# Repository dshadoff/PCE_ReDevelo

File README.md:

# PCE_ReDevelo
A new set of hardware and support code based on Tokumashoten Intermedia's "Develo" magazines from 1996

In 1996, Tokumashoten Intermedia released several "MOOKs" (Magazine-style Books) related
to "Develo System". One for Assembler, one for BASIC, and two issues of a magazine which
followed.  The concept was that everyday users could learn how to program (or develop art
and/or music) for the PC Engine, and somehow they could eventually develop games of their own.

The "Develo System" consisted of three pieces:
1. Software on the PC Engine side (a CD-ROM included with the MOOK)
2. Software on the PC side (targetted at MSX and PC-98 series computers)
3. A small piece of hardware which was used to connect the two systems.  On the PC Engine
   side, it conected to the joypad port (while allowing pass-through for regular
   joypad use), and on the computer side, it connected to the printer port and RS-232
   port of the PC-98 (printer port and "Port2" of MSX).

Back in the day, I wasn't able to get this to work because the IBM PC systems available
in the West were not quite compatible with the PC-98. Also, I didn't know any Japanese,
and all of the documentation was in Japanese.

A version for IBM PC eventually came out, but the release packages were in an obscure
delta patch format sepcific to Japan, and the documentation was still all in Japanese.
I wasn't able to get it working to my satisfaction.

In 1998 or so, David Michel (author of the famous MagicEngine PC Engine emulator) released
an assembler package, which included some basic support for Develo, and I was able to
download the data on the disc, but I didn't do much more than that.

Years later, and computer nowadays don't normally have the same ports, and won't run the
same 16-bit progrmas from back then, so nothing from that time will work - unless you
manage to obtain old machines and put them to use.

This was the inspiration for the ReDevelo system I have created, which also consists of three pieces:
1. Software on the PC Engine side (use the original from the MOOK)
2. Software on the PC side (in Python, for flexibility)
3. A small piece of hardware to connect the two systems (and corresponding firmware).
   Plans are provided, including enough information for small-run production of the PC Boards.

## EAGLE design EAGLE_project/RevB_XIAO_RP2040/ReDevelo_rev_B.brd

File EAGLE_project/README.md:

# PCE_ReDevelo - PC Boards

Here, you will find EAGLE project files for version of the board I have made/used.

The EAGLE project files are included, plus the gerbers and even the PCB assembly files
which might be useful for submission to JLCPCB (these are the BOM and assembly csv files).

### Revision A - Adafruit M0 Adalogger

This was the initial board I used, as I was familiar with it, and have made several designs
based on the board.  However, it has some features which I didn't end up using (and a cost
to go along with those features).

I ended up switching to the Seeeduino XIAO because this is basically a straightforward project.
So far, all code will work on both boards, but my target platform from now on will be the 'Rev B'
hardware, so this board may stop being supported at some point.

### Revision B - Seeeduino XIAO M0

As this project is straightforward, I decided to aim for a board with broad availability and
a low price (as well as a small footprint), so I chose the Seeeduino XIAO M0, which retails
for around US$5.50 .  This device is supported by the Arduino ecosystem, which is used by this
project at the current time.

In future, I may switch over to the Seeeduino XIAO RP2040 - which could sit on the same board,
but if I do that, I would port the Arduino code to the pico-sdk.

In this board revision, I have made the pads larger so that you can choose whether to mount the
XIAO M0 in a socket, or flush with the board (as the XIAO is castellated, and can be soldered
directly to the carrier board).  I also placed mounting holes in preparation for a 3D-printed
case, but have not yet designed one.  (One a case is designed, there may need to be another
board revision to accommodate the physical requirements of the case).

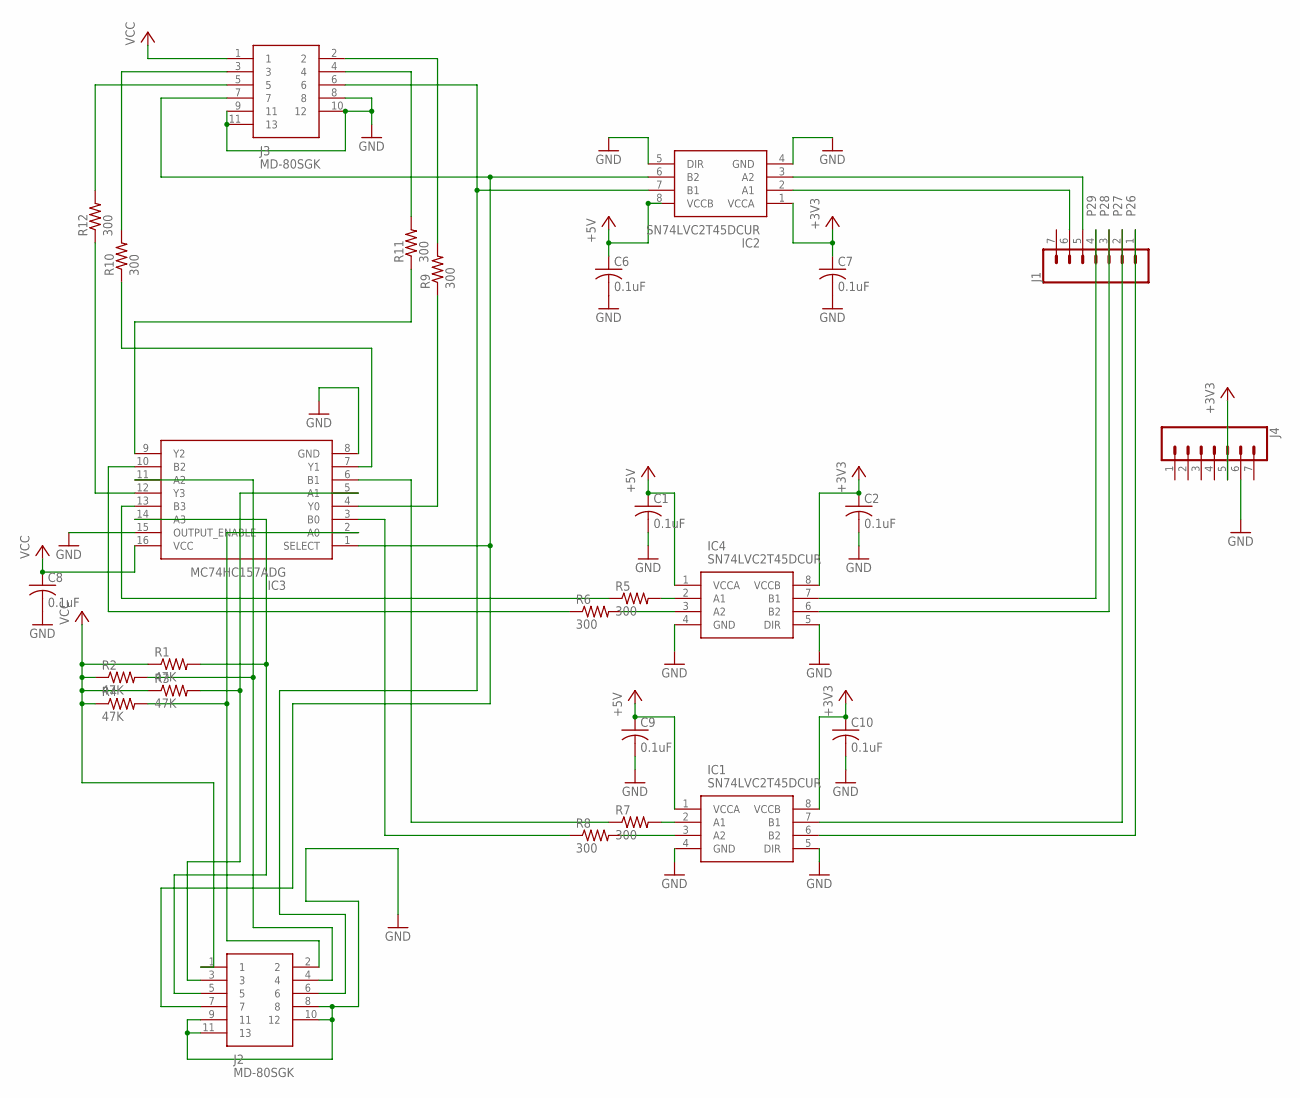
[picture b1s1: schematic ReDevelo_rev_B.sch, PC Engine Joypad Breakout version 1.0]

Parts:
C1, C2, C6, C7, C8, C9, C10: 0.1uF; C0402
IC1, IC2, IC4: SN74LVC2T45DCUR; SOP50P310X90-8N
IC3: MC74HC157ADG; SOIC127P600X175-16N
J1, J4: CONN_071X07_LONGPADS_OFFSET; 1X07_LONGPADS_OFFSET
J2, J3: MD-80SGK; MD80SGK
R1, R2, R3, R4: 47K; R0402
R5, R6, R7, R8, R9, R10, R11, R12: 300; R0402

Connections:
+3V3: C2.1, C7.1, C10.1, IC1.8 (VCCB), IC2.1 (VCCA), IC4.8 (VCCB), J4.5
CLR: IC2.6 (B2), IC3.1 (SELECT), J2.7, J3.7
D12: IC2.2 (A1), J1.6
D13: IC2.3 (A2), J1.5
GND: C1.2, C2.2, C6.2, C7.2, C8.2, C9.2, C10.2, IC1.4 (GND), IC1.5 (DIR), IC2.4 (GND), IC2.5 (DIR), IC3.8 (GND), IC3.15 (OUTPUT_ENABLE), IC4.4 (GND), IC4.5 (DIR), J2.8, J2.9 (11), J2.10 (12), J2.11 (13), J3.8, J3.9 (11), J3.10 (12), J3.11 (13), J4.6
unnamed: IC3.5 (A1), J2.3, R3.2
unnamed: IC3.2 (A0), J2.2, R4.2
unnamed: IC3.11 (A2), J2.4, R2.2
unnamed: IC3.14 (A3), J2.5, R1.2
unnamed: IC3.12 (Y3), R12.1
unnamed: IC3.9 (Y2), R11.1
unnamed: IC3.13 (B3), R5.1
unnamed: IC3.7 (Y1), R10.1
unnamed: IC4.2 (A1), R5.2
unnamed: IC4.3 (A2), R6.2
unnamed: IC1.3 (A2), R8.2
unnamed: IC1.2 (A1), R7.2
unnamed: IC3.10 (B2), R6.1
unnamed: IC3.3 (B0), R8.1
unnamed: IC3.6 (B1), R7.1
unnamed: J3.2, R9.2
unnamed: J3.4, R11.2
unnamed: IC3.4 (Y0), R9.1
unnamed: J3.3, R10.2
unnamed: J3.5, R12.2
P26: IC1.6 (B2), J1.1
P27: IC1.7 (B1), J1.2
P28: IC4.6 (B2), J1.3
P29: IC4.7 (B1), J1.4
SEL: IC2.7 (B1), J2.6, J3.6
VCC: C1.1, C6.1, C8.1, C9.1, IC1.1 (VCCA), IC2.8 (VCCB), IC3.16 (VCC), IC4.1 (VCCA), J2.1, J3.1, R1.1, R2.1, R3.1, R4.1

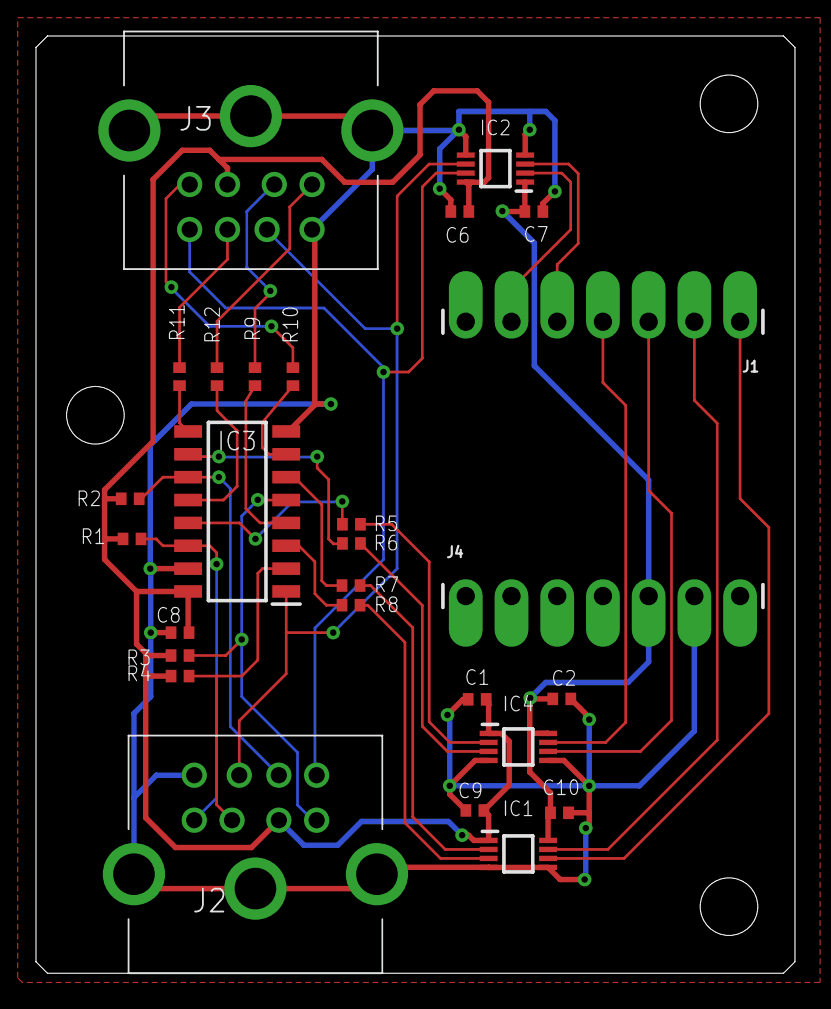
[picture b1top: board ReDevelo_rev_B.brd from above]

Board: 2 copper layers, 42.2 x 52.1 mm, 27 parts (0 on the bottom side), 31 nets.

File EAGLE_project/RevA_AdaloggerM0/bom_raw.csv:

"Qty";"Value";"Device";"Package";"Parts";"Description";"";
"1";"";"HEADER-1X12";"1X12_ROUND";"JP3";"";"";
"1";"";"HEADER-1X16ROUND";"1X16_ROUND";"JP1";"PIN HEADER";"";
"7";"0.1uF";"C-USC0603";"C0603";"C1, C2, C6, C7, C8, C9, C10";"CAPACITOR, American symbol";"";
"8";"300";"R-US_R0603";"R0603";"R5, R6, R7, R8, R9, R10, R11, R12";"RESISTOR, American symbol";"";
"4";"47K";"R-US_R0603";"R0603";"R1, R2, R3, R4";"RESISTOR, American symbol";"";
"1";"MC74HC157ADG";"MC74HC157ADG";"SOIC127P600X175-16N";"IC3";"Source:  Datasheet";"";
"2";"MD-80SGK";"MD-80SGK";"MD80SGK";"J2, J3";"Circular DIN Connectors mini-DIN, 8P jack, rt, through hole, full shield";"";
"3";"SN74LVC2T45DCUR";"SN74LVC2T45DCUR";"SOP50P310X90-8N";"IC1, IC2, IC4";"Texas Instruments SN74LVC2T45DCUR, Voltage Level Translator, Bus Transceiver, 3-State, 1.65  5.5 V, 8-Pin UM";"";

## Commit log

2022-03-27 Initial Check-in
2022-03-28 Add Technical Background update
2022-03-29 Add 'getram' function and get system ROM python script
2022-03-29 clean up getrom
2022-03-30 Add getvram, getpal primitives (and test programs)
2022-03-31 Add Setram, SetVram, setcolor functions ad test programs
2022-03-31 Add exec() and getsector() functions, add a couple of test programs
2022-04-01 Clean up Arduino code
2022-04-03 Start adding comments
2022-04-03 New setbank demo function; prepare to use parameters on command-line tools
2022-04-04 Updates to filenames and command-line parameters
2022-04-12 Add "execute" command
2022-04-12 Fix execute
2022-04-12 Implement get directory from Develo disc
2022-04-13 Improve speed of dir with early exit
2022-04-13 Add functionality to extract file from CDROM ("getfile")
2022-04-16 Add 'execmx' fucntion.
    Tested by extracting 'sound2.mx' from the CD and running it.
    Compared behaviour against the 'sound2.asm' fie's source code
2022-06-18 Update for Seeeduino XIAO version
2022-06-18 Rename firmware path

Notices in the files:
EAGLE_project/RevB_XIAO_RP2040/ReDevelo_rev_B.brd:
(C)2022 David Shadoff
parts and their libraries:
SparkFun-Connectors_new: Licensing: Creative Commons ShareAlike 4.0 International - https://creativecommons.org/licenses/by-sa/4.0
